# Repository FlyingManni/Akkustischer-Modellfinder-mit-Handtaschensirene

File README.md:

# Modellfinder (Ansteuerung eines Taschenalarms)

Um verloren gegangene Modelle leichter wiederzufinden (besonders im Maisfeld), kam die Idee,  
einen Taschenalarm zu verwenden. Um diesen gezielt auszulösen, benötigt man eine entsprechende  
Ansteuerung — hier kommt der **Tiny45 Modellfinder** zum Einsatz.

---

## 🧭 Tiny45 Steuerung

Der Modellfinder wird über einen freien Empfängerkanal gesteuert.  
Hierbei gibt es vier mögliche Zustände:

1. **Empfängersignal kleiner 1,4 ms**  
   → Schaltet den Alarm scharf und ist ausgeschaltet.  
   Solange nicht mindestens einmalig ein Signal unter 1,4 ms anlag, ist keine Alarmierung möglich.  
   Wenn der Alarm *scharf* und ausgeschaltet ist, leuchtet die **Status-LED dauerhaft**.

2. **Signal zwischen 1,4 und 1,7 ms**  
   → Das sollte auch die *Failsafe-Einstellung* sein.  
   Liegt dieses Signal an, startet ein **1-minütiger Timer**.  
   Nach Ablauf von 1 Minute wird der Alarm ausgelöst.  
   Während der Timer läuft, **blinkt die Status-LED schnell**.

3. **Signal über 1,7 ms**  
   → Es wird **sofort Alarm ausgelöst**.  
   Die **Status-LED blinkt langsam**.

4. **Kein Signal mehr vom Empfänger**  
   (z. B. wenn der Flugakku vom Modell getrennt wurde)  
   → Ablauf wie bei Zustand 2.

> 🧩 **Anmerkung:**  
> Zustände 2 bis 4 sind erst möglich, wenn zuvor einmal Zustand 1 hergestellt wurde  
> (also ein Empfängersignal unter 1,4 ms anlag).

---

## 🔌 Anschlussübersicht

| Pin        | Funktion / Anschlussbeschreibung |
|-------------|---------------------------------|
| **RC-Signal** | An einen Empfängerausgang (Signal) anschließen |
| **RC-GND**    | Masse des Empfängerausgangs |
| **+UB**       | Betriebsspannung des Alarmgebers **max. 5V** (nicht direkt an Batterie-Plus anschließen, sondern an die Buchse, über die der Alarm ursprünglich ausgelöst wird – sonst ist die Steuerung ständig aktiv und die Batterie bald leer) |
| **Alarm**     | Schaltet gegen Masse – hier wird die vorhandene Alarmschaltung angeschlossen |
| **GND**       | Direkt an den Minuspol der Batterie anschließen |

---

## 📦 Tiny45 Steuerung

---

## 📘 Lizenz & Hinweise

Dieses Projekt ist für den privaten Gebrauch gedacht.  
Verwendung auf eigene Verantwortung.

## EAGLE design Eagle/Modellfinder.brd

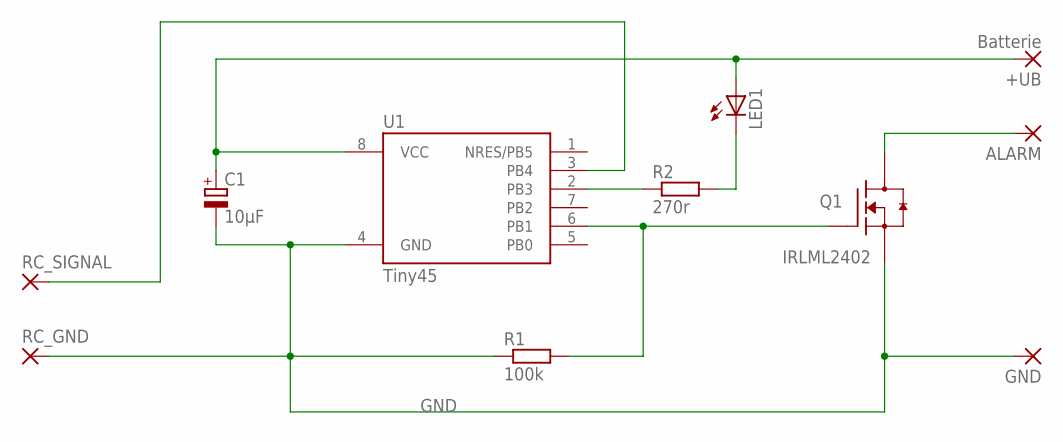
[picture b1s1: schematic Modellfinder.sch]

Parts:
+UB: Batterie; SMD1,27-2,54
ALARM: SMD2; SMD1,27-2,54
C1: 10µF; 085CS_1AR
GND: SMD2; SMD1,27-2,54
LED1: LEDSML0805; SML0805
Q1: IRLML2402; SOT95P280X135-3N
R1: 100k; M1206
R2: 270r; M1206
RC_GND: SMD2; SMD1,27-2,54
RC_SIGNAL: SMD2; SMD1,27-2,54
U1: Tiny45; SOIC8_EIAJ_208MIL

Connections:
GND: C1.-, GND.1, Q1.2 (S), R1.1, RC_GND.1, U1.4 (GND)
unnamed: Q1.1 (G), R1.2, U1.6 (PB1)
unnamed: LED1.C, R2.2
unnamed: +UB.1, C1.+, LED1.A, U1.8 (VCC)
unnamed: ALARM.1, Q1.3 (D)
unnamed: RC_SIGNAL.1, U1.3 (PB4)
unnamed: R2.1, U1.2 (PB3)

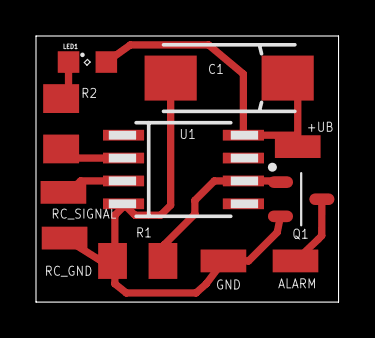
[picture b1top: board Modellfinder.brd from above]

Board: 2 copper layers, 16.8 x 14.8 mm, 11 parts (0 on the bottom side), 7 nets.

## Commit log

2025-10-10 Add files via upload
    zeigt wie man über einen RC-Sender manuell einne Alarm startet (RC Ausgang + 100%)
